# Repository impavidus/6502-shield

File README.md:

# 6502-shield

An Arduino shield that provides a 6502 cpu, ram, rom, and pio compactly.

## Project Status

I'm about to order the first prototype PCBs from OSH Park.  That means this PCB is completely untested and quite likely may burst into flames when powered on.  However, I am by no means here to tell you how to live your life so if you want to make one... =)

## Introduction

The 6502 shield provides (err will provide) most of the major components needed to implement a 6502 based computer.  Some of the key features.  This is aspirational and subject to change.

* Fully static design allows for single step execution of programs
* W65C02S - 8 bit CPU, W65C22 PIO controller, AT28BV256 256K EEPROM, AS6C62256 256K SRAM
* Full access to PIO PORTA and PORTB via header
* LCD header with potentiometer provides power, ground, and contrast adjust
* All components are leaded and reachable with mini-grabbers
* Support for optional DIP-8/4 3.3V External Crystal Oscillator
* Clock select jumper allows board to run from Internal FPGA clock or External XO
* LED status indicators for R/W, IRQ, CLK pins
* LED status indicators show when a devices address space is being accessed by the CPU (RAM/ROM/PIO/FPGA)
* FPGA manages chip enables based on user defined memory map.
* EEPROM write protection for EEPROM address space.
* EEPROM is programmed directly by Arduino asserting EEPROM_PGM line. This also disables EEPROM write protection in place during normal operation.
* DMA access from the Arduino to the 256K SRAM supported by asserting DMA line.
* FPGA clock supports run/halt/step via on-board push-button and slide switches.

## PCB

## Schematic

A PDF version of the schematic is <a href="docs/6502-shield-schematic.pdf">here</a>.

## System Block Diagram

## Source Files

All of the schematic capture and board layout work was done with Eagle.  The component libraries used, .sch, and .brd files are provided.

## CAM Files

All CAM files needed for PCB manufacturing including silkscreens, drills, etc. are provided.  In addition pick and place files and a Bill of Materials is provided in the CAMOutputs/Assembly folder.

## Models

The 3d model was done with AutoDesk Fusion.  The source file as well as .STEP file for the completed shield is provided.

## FPGA

The FPGA work is all going to be done in VHDL.  Once I begin writing it, I will add all of the source files, testbenches, etc. to the repository.

## 6502 Code

Also plan to provide some simple example assembly that demonstrates all the boards functions are working.  This will also be added to the repository.

## Acknowledgements

* Ben Eater - His breadboard computer projects are making homebrew cool again.  Ben's work heavily influenced my decision to attempt this project as well as inspiring me to make it all open and available for anyone.  If you're just getting started, please start with Ben's site, even if you don't build the breadboards yourself (but you should if at all possible) - seriously -  Thanks Ben.  < http://eater.net >

* Daryl Rictor - Thank you Daryl for sharing your Memory Decoder GAL based design to achieve a flexible memory map.  I am applying your approach in the FPGA of my design. < http://sbc.rictor.org/decoder.html >

* r/beneater - Pretty cool community even though I'm a lurker.  Seeing everybody else's builds made me give it a try, thanks for that everyone.  https://reddit.com/r/beneater

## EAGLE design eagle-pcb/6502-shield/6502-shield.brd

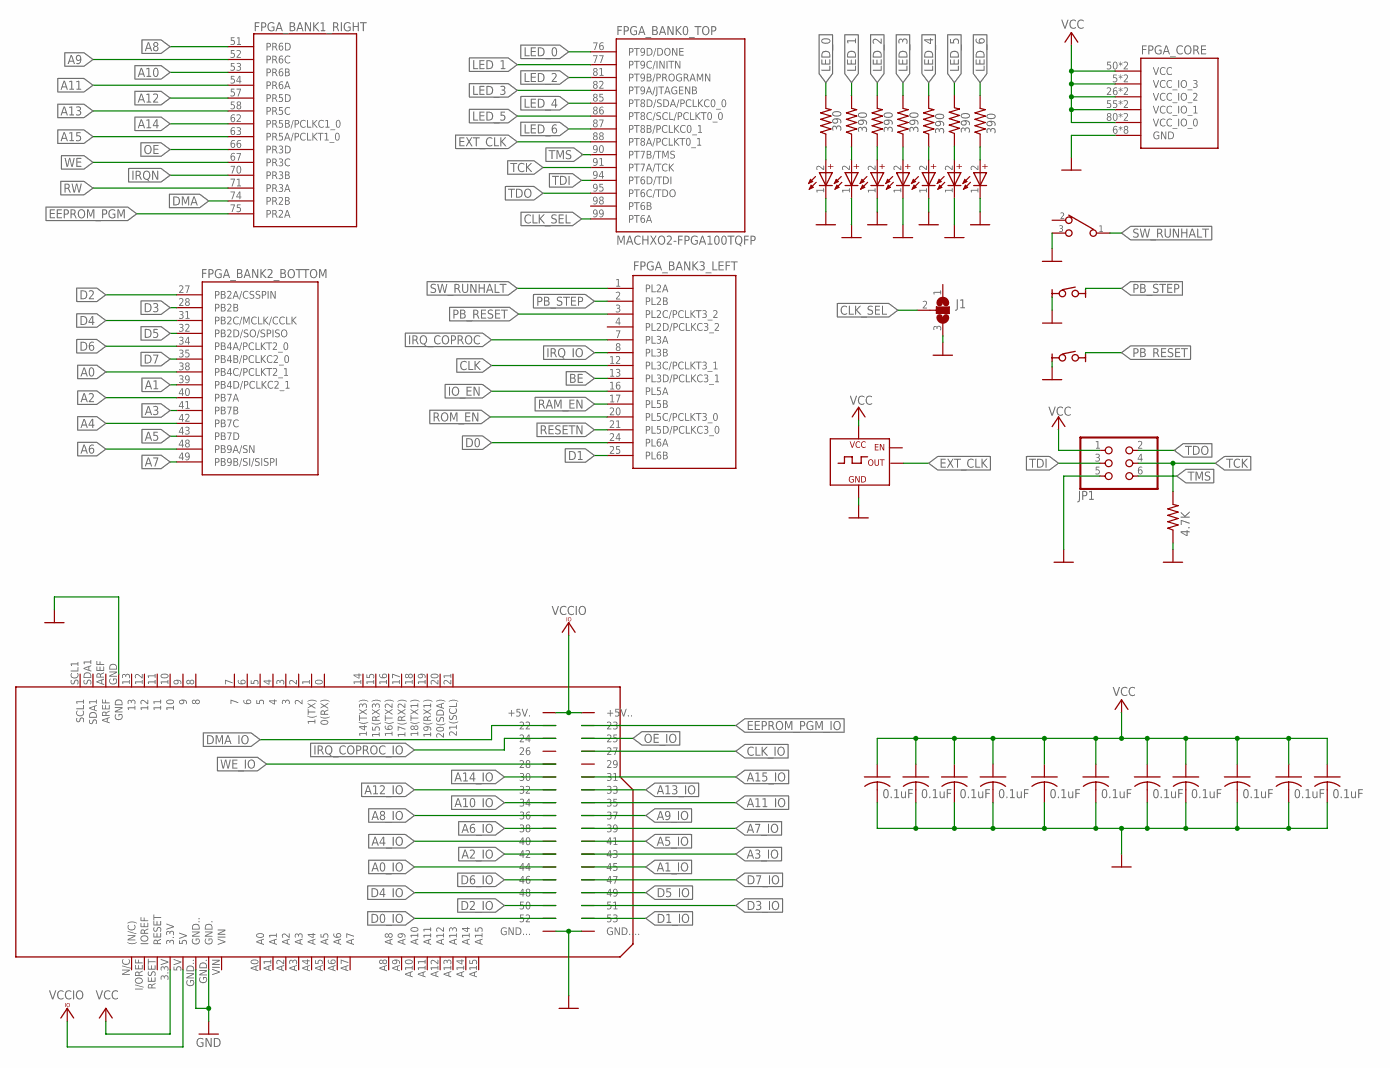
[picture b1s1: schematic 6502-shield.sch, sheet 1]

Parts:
C1, C2, C3, C4, C5, C6, C7, C20, C21, C22, C23: 0.1uF; C0805
D1, D2, D3, D4, D5, D6, D7: RED; WL-SMCD_0603
EXT_XO: CRYSTAL-OSC-DIP8/4; DIP8/4
FPGA: MACHXO2-FPGA100TQFP; QFP50P1600X1600X160-100N
J1: SJ2W; SJ_2
JP1: PINHD-2X3; 2X03
PB_RESET: MCSLPT4644B1TR-TACT-SW; MCSLPT4644B1TR-TACT-SW-NEW
PB_STEP: MCSLPT4644B1TR-TACT-SW; MCSLPT4644B1TR-TACT-SW-NEW
PCB1: ARDUINO_MEGA2560
R2, R4, R5, R6, R7, R8, R9: 390; R0603
R3: 4.7K; R0603
SW_RUNHALT: PCM12SMTR-SPDT-RIGHT-ANG; PCM12SMTR

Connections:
A0: FPGA.38 (PB4C/PCLKT2_1); also elsewhere on the board
A0_IO: PCB1.44; also elsewhere on the board
A1: FPGA.39 (PB4D/PCLKC2_1); also elsewhere on the board
A1_IO: PCB1.45; also elsewhere on the board
A2: FPGA.40 (PB7A); also elsewhere on the board
A2_IO: PCB1.42; also elsewhere on the board
A3: FPGA.41 (PB7B); also elsewhere on the board
A3_IO: PCB1.43; also elsewhere on the board
A4: FPGA.42 (PB7C); also elsewhere on the board
A4_IO: PCB1.40; also elsewhere on the board
A5: FPGA.43 (PB7D); also elsewhere on the board
A5_IO: PCB1.41; also elsewhere on the board
A6: FPGA.48 (PB9A/SN); also elsewhere on the board
A6_IO: PCB1.38; also elsewhere on the board
A7: FPGA.49 (PB9B/SI/SISPI); also elsewhere on the board
A7_IO: PCB1.39; also elsewhere on the board
A8: FPGA.51 (PR6D); also elsewhere on the board
A8_IO: PCB1.36; also elsewhere on the board
A9: FPGA.52 (PR6C); also elsewhere on the board
A9_IO: PCB1.37; also elsewhere on the board
A10: FPGA.53 (PR6B); also elsewhere on the board
A10_IO: PCB1.34; also elsewhere on the board
A11: FPGA.54 (PR6A); also elsewhere on the board
A11_IO: PCB1.35; also elsewhere on the board
A12: FPGA.57 (PR5D); also elsewhere on the board
A12_IO: PCB1.32; also elsewhere on the board
A13: FPGA.58 (PR5C); also elsewhere on the board
A13_IO: PCB1.33; also elsewhere on the board
A14: FPGA.62 (PR5B/PCLKC1_0); also elsewhere on the board
A14_IO: PCB1.30; also elsewhere on the board
A15: FPGA.63 (PR5A/PCLKT1_0); also elsewhere on the board
A15_IO: PCB1.31; also elsewhere on the board
BE: FPGA.13 (PL3D/PCLKC3_1); also elsewhere on the board
CLK: FPGA.12 (PL3C/PCLKT3_1); also elsewhere on the board
CLK_IO: PCB1.27; also elsewhere on the board
CLK_SEL: FPGA.99 (PT6A), J1.2
D0: FPGA.24 (PL6A); also elsewhere on the board
D0_IO: PCB1.52; also elsewhere on the board
D1: FPGA.25 (PL6B); also elsewhere on the board
D1_IO: PCB1.53; also elsewhere on the board
D2: FPGA.27 (PB2A/CSSPIN); also elsewhere on the board
D2_IO: PCB1.50; also elsewhere on the board
D3: FPGA.28 (PB2B); also elsewhere on the board
D3_IO: PCB1.51; also elsewhere on the board
D4: FPGA.31 (PB2C/MCLK/CCLK); also elsewhere on the board
D4_IO: PCB1.48; also elsewhere on the board
D5: FPGA.32 (PB2D/SO/SPISO); also elsewhere on the board
D5_IO: PCB1.49; also elsewhere on the board
D6: FPGA.34 (PB4A/PCLKT2_0); also elsewhere on the board
D6_IO: PCB1.46; also elsewhere on the board
D7: FPGA.35 (PB4B/PCLKC2_0); also elsewhere on the board
D7_IO: PCB1.47; also elsewhere on the board
DMA: FPGA.74 (PR2B); also elsewhere on the board
DMA_IO: PCB1.22; also elsewhere on the board
EEPROM_PGM: FPGA.75 (PR2A); also elsewhere on the board
EEPROM_PGM_IO: PCB1.23; also elsewhere on the board
EXT_CLK: EXT_XO.5 (OUT), FPGA.88 (PT8A/PCLKT0_1)
GND: C1.2, C2.2, C3.2, C4.2, C5.2, C6.2, C7.2, C20.2, C21.2, C22.2, C23.2, D1.1 (C), D2.1 (C), D3.1 (C), D4.1 (C), D5.1 (C), D6.1 (C), D7.1 (C), EXT_XO.4 (GND), FPGA.6 (GND), FPGA.22 (GND), FPGA.33 (GND), FPGA.44 (GND), FPGA.56 (GND), FPGA.72 (GND), FPGA.79 (GND), FPGA.92 (GND), J1.3, JP1.5, PB_RESET.T2, PB_STEP.T2, PCB1.GND, PCB1.GND., PCB1.GND.., PCB1.GND..., PCB1.GND...., R3.1, SW_RUNHALT.3; also elsewhere on the board
IO_EN: FPGA.16 (PL5A); also elsewhere on the board
IRQN: FPGA.70 (PR3B); also elsewhere on the board
IRQ_COPROC: FPGA.7 (PL3A); also elsewhere on the board
IRQ_COPROC_IO: PCB1.24; also elsewhere on the board
IRQ_IO: FPGA.8 (PL3B); also elsewhere on the board
LED_0: FPGA.76 (PT9D/DONE), R5.2
LED_1: FPGA.77 (PT9C/INITN), R6.2
LED_2: FPGA.81 (PT9B/PROGRAMN), R7.2
LED_3: FPGA.82 (PT9A/JTAGENB), R8.2
LED_4: FPGA.85 (PT8D/SDA/PCLKC0_0), R9.2
LED_5: FPGA.86 (PT8C/SCL/PCLKT0_0), R4.2
LED_6: FPGA.87 (PT8B/PCLKC0_1), R2.2
unnamed: D1.2 (A), R5.1
unnamed: D2.2 (A), R6.1
unnamed: D5.2 (A), R7.1
unnamed: D4.2 (A), R8.1
unnamed: D3.2 (A), R9.1
unnamed: D6.2 (A), R4.1
unnamed: D7.2 (A), R2.1
OE: FPGA.66 (PR3D); also elsewhere on the board
OE_IO: PCB1.25; also elsewhere on the board
PB_RESET: FPGA.3 (PL2C/PCLKT3_2), PB_RESET.T3
PB_STEP: FPGA.2 (PL2B), PB_STEP.T3
RAM_EN: FPGA.17 (PL5B); also elsewhere on the board
RESETN: FPGA.21 (PL5D/PCLKC3_0); also elsewhere on the board
ROM_EN: FPGA.20 (PL5C/PCLKT3_0); also elsewhere on the board
RW: FPGA.71 (PR3A); also elsewhere on the board
SW_RUNHALT: FPGA.1 (PL2A), SW_RUNHALT.1
TCK: FPGA.91 (PT7A/TCK), JP1.4, R3.2
TDI: FPGA.94 (PT6D/TDI), JP1.3
TDO: FPGA.95 (PT6C/TDO), JP1.2
TMS: FPGA.90 (PT7B/TMS), JP1.6
VCC: C1.1, C2.1, C3.1, C4.1, C5.1, C6.1, C7.1, C20.1, C21.1, C22.1, C23.1, EXT_XO.8 (VCC), FPGA.5 (VCC_IO_3), FPGA.23 (VCC_IO_3), FPGA.26 (VCC_IO_2), FPGA.46 (VCC_IO_2), FPGA.50 (VCC), FPGA.55 (VCC_IO_1), FPGA.73 (VCC_IO_1), FPGA.80 (VCC_IO_0), FPGA.93 (VCC_IO_0), FPGA.100 (VCC), JP1.1, PCB1.3.3V; also elsewhere on the board
VCCIO: PCB1.5V, PCB1.5V. (+5V.), PCB1.5V.. (+5V..); also elsewhere on the board
WE: FPGA.67 (PR3C); also elsewhere on the board
WE_IO: PCB1.28; also elsewhere on the board

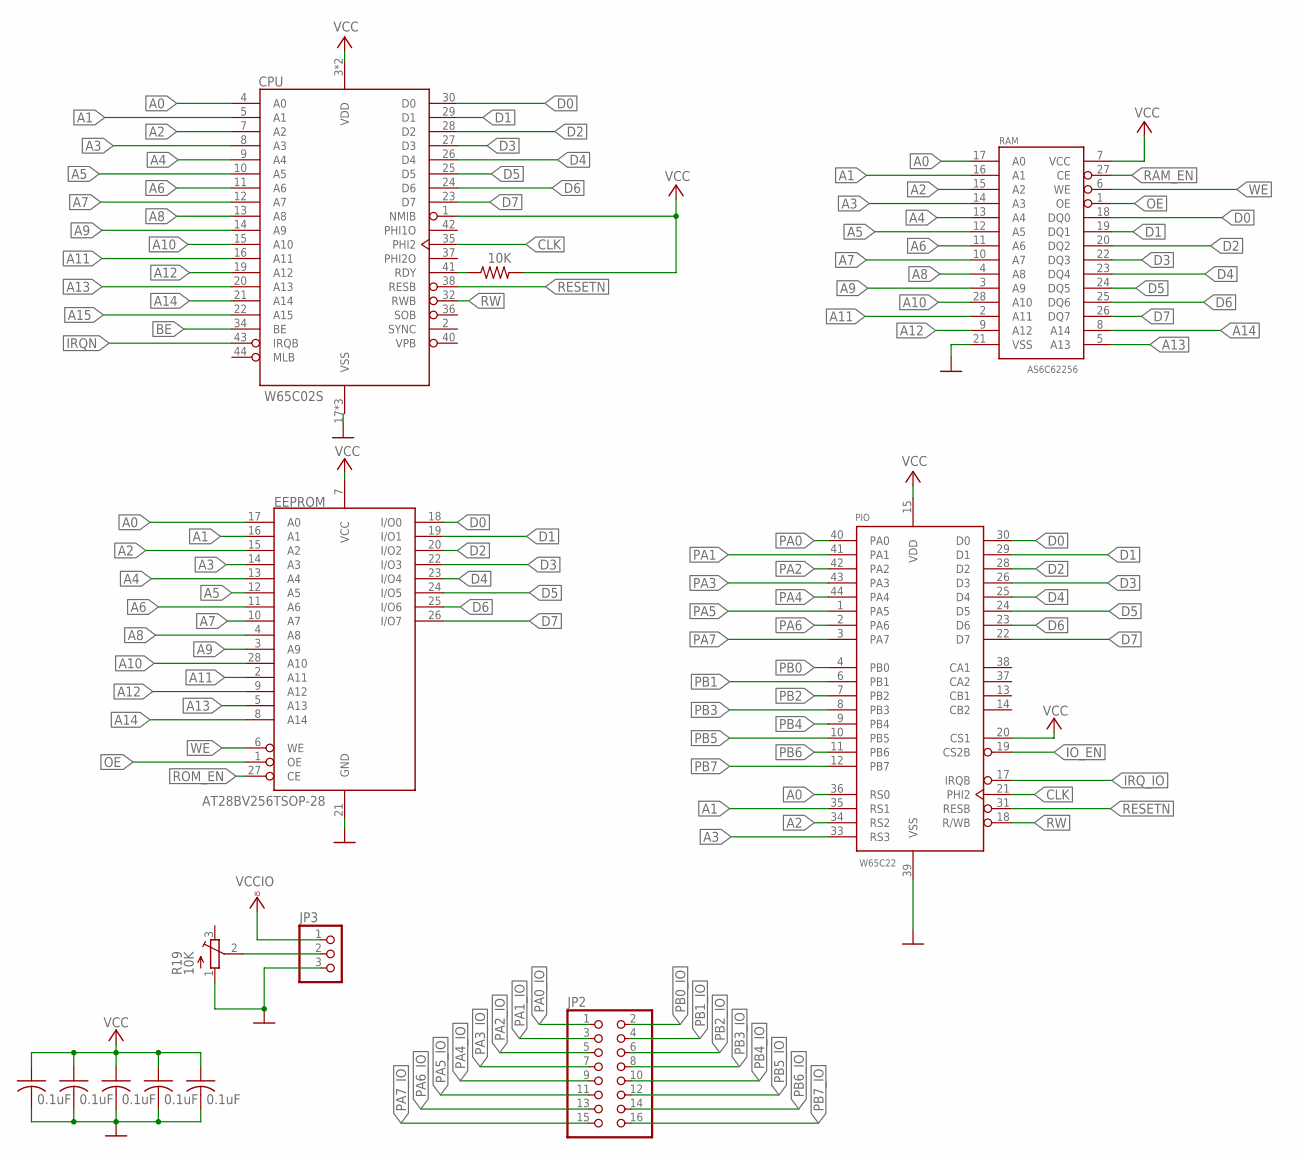
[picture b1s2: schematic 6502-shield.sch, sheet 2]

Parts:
C24, C25, C26, C27, C28: 0.1uF; C0805
CPU: W65C02S; QFP80P1320X1320X270-44N
EEPROM: AT28BV256TSOP-28; SOP55P1340X120-28N
JP2: PINHD-2X8; 2X08
JP3: PINHD-1X3; 1X03
PIO: W65C22; QFP80P1320X1320X270-44N
R18: 10K; R0603
R19: 10K; TC33X
RAM: AS6C62256; SOP55P1340X120-28N

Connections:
A0: CPU.4 (A0), EEPROM.17 (A0), PIO.36 (RS0), RAM.17 (A0); also elsewhere on the board
A1: CPU.5 (A1), EEPROM.16 (A1), PIO.35 (RS1), RAM.16 (A1); also elsewhere on the board
A2: CPU.7 (A2), EEPROM.15 (A2), PIO.34 (RS2), RAM.15 (A2); also elsewhere on the board
A3: CPU.8 (A3), EEPROM.14 (A3), PIO.33 (RS3), RAM.14 (A3); also elsewhere on the board
A4: CPU.9 (A4), EEPROM.13 (A4), RAM.13 (A4); also elsewhere on the board
A5: CPU.10 (A5), EEPROM.12 (A5), RAM.12 (A5); also elsewhere on the board
A6: CPU.11 (A6), EEPROM.11 (A6), RAM.11 (A6); also elsewhere on the board
A7: CPU.12 (A7), EEPROM.10 (A7), RAM.10 (A7); also elsewhere on the board
A8: CPU.13 (A8), EEPROM.4 (A8), RAM.4 (A8); also elsewhere on the board
A9: CPU.14 (A9), EEPROM.3 (A9), RAM.3 (A9); also elsewhere on the board
A10: CPU.15 (A10), EEPROM.28 (A10), RAM.28 (A10); also elsewhere on the board
A11: CPU.16 (A11), EEPROM.2 (A11), RAM.2 (A11); also elsewhere on the board
A12: CPU.19 (A12), EEPROM.9 (A12), RAM.9 (A12); also elsewhere on the board
A13: CPU.20 (A13), EEPROM.5 (A13), RAM.5 (A13); also elsewhere on the board
A14: CPU.21 (A14), EEPROM.8 (A14), RAM.8 (A14); also elsewhere on the board
A15: CPU.22 (A15); also elsewhere on the board
BE: CPU.34 (BE); also elsewhere on the board
CLK: CPU.35 (PHI2), PIO.21 (PHI2); also elsewhere on the board
D0: CPU.30 (D0), EEPROM.18 (I/O0), PIO.30 (D0), RAM.18 (DQ0); also elsewhere on the board
D1: CPU.29 (D1), EEPROM.19 (I/O1), PIO.29 (D1), RAM.19 (DQ1); also elsewhere on the board
D2: CPU.28 (D2), EEPROM.20 (I/O2), PIO.28 (D2), RAM.20 (DQ2); also elsewhere on the board
D3: CPU.27 (D3), EEPROM.22 (I/O3), PIO.26 (D3), RAM.22 (DQ3); also elsewhere on the board
D4: CPU.26 (D4), EEPROM.23 (I/O4), PIO.25 (D4), RAM.23 (DQ4); also elsewhere on the board
D5: CPU.25 (D5), EEPROM.24 (I/O5), PIO.24 (D5), RAM.24 (DQ5); also elsewhere on the board
D6: CPU.24 (D6), EEPROM.25 (I/O6), PIO.23 (D6), RAM.25 (DQ6); also elsewhere on the board
D7: CPU.23 (D7), EEPROM.26 (I/O7), PIO.22 (D7), RAM.26 (DQ7); also elsewhere on the board
GND: C24.2, C25.2, C26.2, C27.2, C28.2, EEPROM.21 (GND), JP3.3, PIO.39 (VSS), R19.1 (A), RAM.21 (VSS); also elsewhere on the board
IO_EN: PIO.19 (CS2B); also elsewhere on the board
IRQN: CPU.43 (IRQB); also elsewhere on the board
IRQ_IO: PIO.17 (IRQB); also elsewhere on the board
unnamed: CPU.41 (RDY), R18.1
unnamed: JP3.2, R19.2 (S)
OE: EEPROM.1 (OE), RAM.1 (OE); also elsewhere on the board
PA0: PIO.40 (PA0); also elsewhere on the board
PA0_IO: JP2.1; also elsewhere on the board
PA1: PIO.41 (PA1); also elsewhere on the board
PA1_IO: JP2.3; also elsewhere on the board
PA2: PIO.42 (PA2); also elsewhere on the board
PA2_IO: JP2.5; also elsewhere on the board
PA3: PIO.43 (PA3); also elsewhere on the board
PA3_IO: JP2.7; also elsewhere on the board
PA4: PIO.44 (PA4); also elsewhere on the board
PA4_IO: JP2.9; also elsewhere on the board
PA5: PIO.1 (PA5); also elsewhere on the board
PA5_IO: JP2.11; also elsewhere on the board
PA6: PIO.2 (PA6); also elsewhere on the board
PA6_IO: JP2.13; also elsewhere on the board
PA7: PIO.3 (PA7); also elsewhere on the board
PA7_IO: JP2.15; also elsewhere on the board
PB0: PIO.4 (PB0); also elsewhere on the board
PB0_IO: JP2.2; also elsewhere on the board
PB1: PIO.6 (PB1); also elsewhere on the board
PB1_IO: JP2.4; also elsewhere on the board
PB2: PIO.7 (PB2); also elsewhere on the board
PB2_IO: JP2.6; also elsewhere on the board
PB3: PIO.8 (PB3); also elsewhere on the board
PB3_IO: JP2.8; also elsewhere on the board
PB4: PIO.9 (PB4); also elsewhere on the board
PB4_IO: JP2.10; also elsewhere on the board
PB5: PIO.10 (PB5); also elsewhere on the board
PB5_IO: JP2.12; also elsewhere on the board
PB6: PIO.11 (PB6); also elsewhere on the board
PB6_IO: JP2.14; also elsewhere on the board
PB7: PIO.12 (PB7); also elsewhere on the board
PB7_IO: JP2.16; also elsewhere on the board
RAM_EN: RAM.27 (CE); also elsewhere on the board
RESETN: CPU.38 (RESB), PIO.31 (RESB); also elsewhere on the board
ROM_EN: EEPROM.27 (CE); also elsewhere on the board
RW: CPU.32 (RWB), PIO.18 (R/WB); also elsewhere on the board
VCC: C24.1, C25.1, C26.1, C27.1, C28.1, CPU.1 (NMIB), CPU.3 (VDD), CPU.31 (VDD), EEPROM.7 (VCC), PIO.15 (VDD), PIO.20 (CS1), R18.2, RAM.7 (VCC); also elsewhere on the board
VCCIO: JP3.1; also elsewhere on the board
WE: EEPROM.6 (WE), RAM.6 (WE); also elsewhere on the board

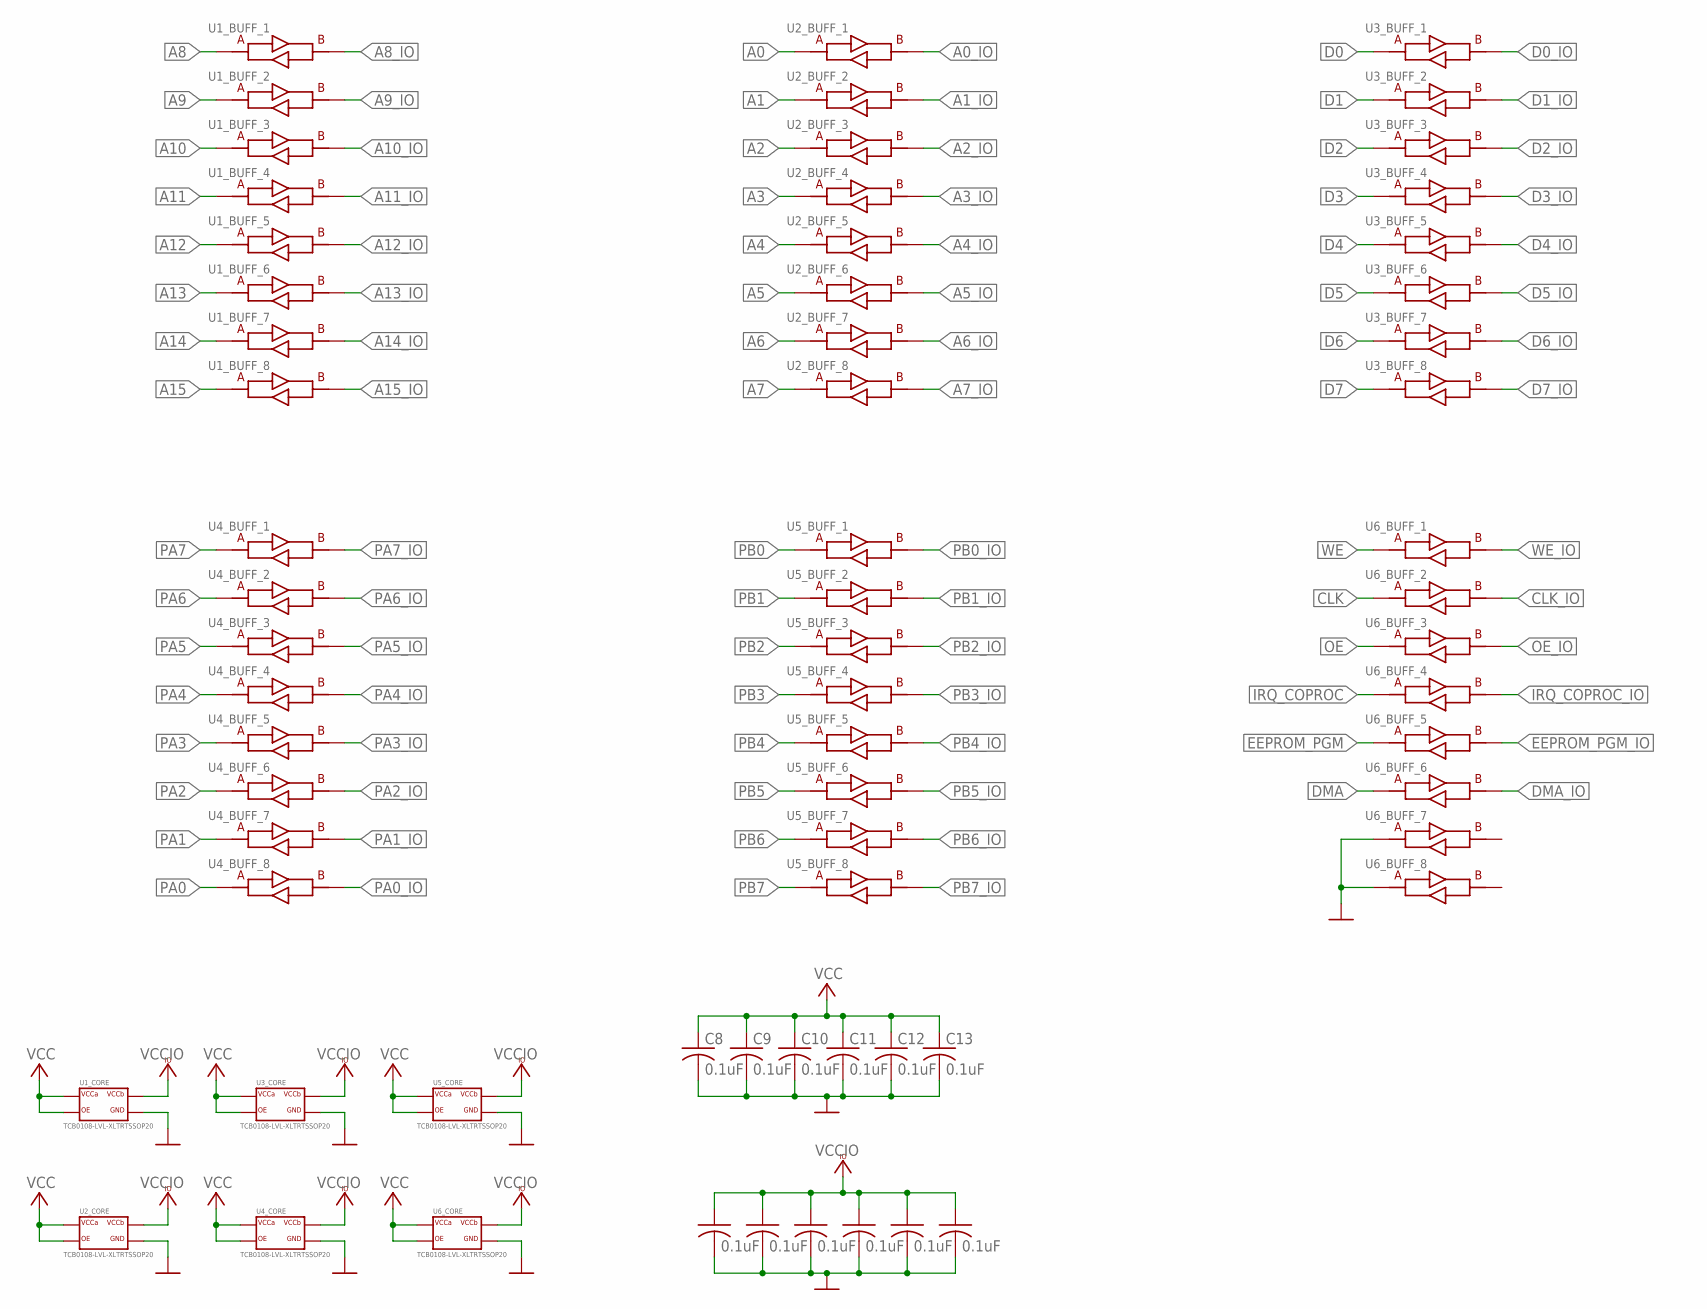
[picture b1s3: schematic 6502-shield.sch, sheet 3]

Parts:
C8, C9, C10, C11, C12, C13, C14, C15, C16, C17, C18, C19: 0.1uF; C0805
U1, U2, U3, U4, U5, U6: TCB0108-LVL-XLTRTSSOP20; SOP65P640X120-20N

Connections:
A0: U2.1 (A); also elsewhere on the board
A0_IO: U2.20 (B); also elsewhere on the board
A1: U2.3 (A); also elsewhere on the board
A1_IO: U2.18 (B); also elsewhere on the board
A2: U2.4 (A); also elsewhere on the board
A2_IO: U2.17 (B); also elsewhere on the board
A3: U2.5 (A); also elsewhere on the board
A3_IO: U2.16 (B); also elsewhere on the board
A4: U2.6 (A); also elsewhere on the board
A4_IO: U2.15 (B); also elsewhere on the board
A5: U2.7 (A); also elsewhere on the board
A5_IO: U2.14 (B); also elsewhere on the board
A6: U2.8 (A); also elsewhere on the board
A6_IO: U2.13 (B); also elsewhere on the board
A7: U2.9 (A); also elsewhere on the board
A7_IO: U2.12 (B); also elsewhere on the board
A8: U1.1 (A); also elsewhere on the board
A8_IO: U1.20 (B); also elsewhere on the board
A9: U1.3 (A); also elsewhere on the board
A9_IO: U1.18 (B); also elsewhere on the board
A10: U1.4 (A); also elsewhere on the board
A10_IO: U1.17 (B); also elsewhere on the board
A11: U1.5 (A); also elsewhere on the board
A11_IO: U1.16 (B); also elsewhere on the board
A12: U1.6 (A); also elsewhere on the board
A12_IO: U1.15 (B); also elsewhere on the board
A13: U1.7 (A); also elsewhere on the board
A13_IO: U1.14 (B); also elsewhere on the board
A14: U1.8 (A); also elsewhere on the board
A14_IO: U1.13 (B); also elsewhere on the board
A15: U1.9 (A); also elsewhere on the board
A15_IO: U1.12 (B); also elsewhere on the board
CLK: U6.3 (A); also elsewhere on the board
CLK_IO: U6.18 (B); also elsewhere on the board
D0: U3.1 (A); also elsewhere on the board
D0_IO: U3.20 (B); also elsewhere on the board
D1: U3.3 (A); also elsewhere on the board
D1_IO: U3.18 (B); also elsewhere on the board
D2: U3.4 (A); also elsewhere on the board
D2_IO: U3.17 (B); also elsewhere on the board
D3: U3.5 (A); also elsewhere on the board
D3_IO: U3.16 (B); also elsewhere on the board
D4: U3.6 (A); also elsewhere on the board
D4_IO: U3.15 (B); also elsewhere on the board
D5: U3.7 (A); also elsewhere on the board
D5_IO: U3.14 (B); also elsewhere on the board
D6: U3.8 (A); also elsewhere on the board
D6_IO: U3.13 (B); also elsewhere on the board
D7: U3.9 (A); also elsewhere on the board
D7_IO: U3.12 (B); also elsewhere on the board
DMA: U6.7 (A); also elsewhere on the board
DMA_IO: U6.14 (B); also elsewhere on the board
EEPROM_PGM: U6.6 (A); also elsewhere on the board
EEPROM_PGM_IO: U6.15 (B); also elsewhere on the board
GND: C8.2, C9.2, C10.2, C11.2, C12.2, C13.2, C14.2, C15.2, C16.2, C17.2, C18.2, C19.2, U1.11 (GND), U2.11 (GND), U3.11 (GND), U4.11 (GND), U5.11 (GND), U6.8 (A), U6.9 (A), U6.11 (GND); also elsewhere on the board
IRQ_COPROC: U6.5 (A); also elsewhere on the board
IRQ_COPROC_IO: U6.16 (B); also elsewhere on the board
OE: U6.4 (A); also elsewhere on the board
OE_IO: U6.17 (B); also elsewhere on the board
PA0: U4.9 (A); also elsewhere on the board
PA0_IO: U4.12 (B); also elsewhere on the board
PA1: U4.8 (A); also elsewhere on the board
PA1_IO: U4.13 (B); also elsewhere on the board
PA2: U4.7 (A); also elsewhere on the board
PA2_IO: U4.14 (B); also elsewhere on the board
PA3: U4.6 (A); also elsewhere on the board
PA3_IO: U4.15 (B); also elsewhere on the board
PA4: U4.5 (A); also elsewhere on the board
PA4_IO: U4.16 (B); also elsewhere on the board
PA5: U4.4 (A); also elsewhere on the board
PA5_IO: U4.17 (B); also elsewhere on the board
PA6: U4.3 (A); also elsewhere on the board
PA6_IO: U4.18 (B); also elsewhere on the board
PA7: U4.1 (A); also elsewhere on the board
PA7_IO: U4.20 (B); also elsewhere on the board
PB0: U5.1 (A); also elsewhere on the board
PB0_IO: U5.20 (B); also elsewhere on the board
PB1: U5.3 (A); also elsewhere on the board
PB1_IO: U5.18 (B); also elsewhere on the board
PB2: U5.4 (A); also elsewhere on the board
PB2_IO: U5.17 (B); also elsewhere on the board
PB3: U5.5 (A); also elsewhere on the board
PB3_IO: U5.16 (B); also elsewhere on the board
PB4: U5.6 (A); also elsewhere on the board
PB4_IO: U5.15 (B); also elsewhere on the board
PB5: U5.7 (A); also elsewhere on the board
PB5_IO: U5.14 (B); also elsewhere on the board
PB6: U5.8 (A); also elsewhere on the board
PB6_IO: U5.13 (B); also elsewhere on the board
PB7: U5.9 (A); also elsewhere on the board
PB7_IO: U5.12 (B); also elsewhere on the board
VCC: C8.1, C9.1, C10.1, C11.1, C12.1, C13.1, U1.2 (VCC_A), U1.10 (OE), U2.2 (VCC_A), U2.10 (OE), U3.2 (VCC_A), U3.10 (OE), U4.2 (VCC_A), U4.10 (OE), U5.2 (VCC_A), U5.10 (OE), U6.2 (VCC_A), U6.10 (OE); also elsewhere on the board
VCCIO: C14.1, C15.1, C16.1, C17.1, C18.1, C19.1, U1.19 (VCC_B), U2.19 (VCC_B), U3.19 (VCC_B), U4.19 (VCC_B), U5.19 (VCC_B), U6.19 (VCC_B); also elsewhere on the board
WE: U6.1 (A); also elsewhere on the board
WE_IO: U6.20 (B); also elsewhere on the board

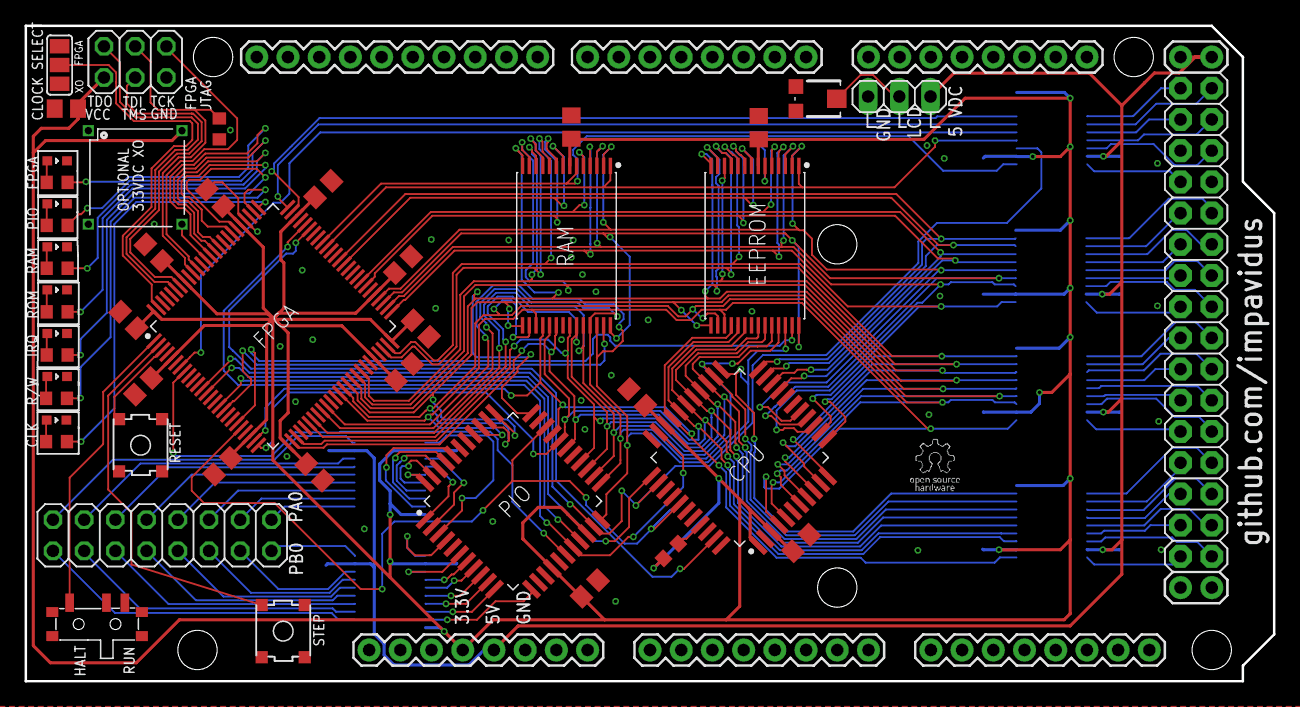
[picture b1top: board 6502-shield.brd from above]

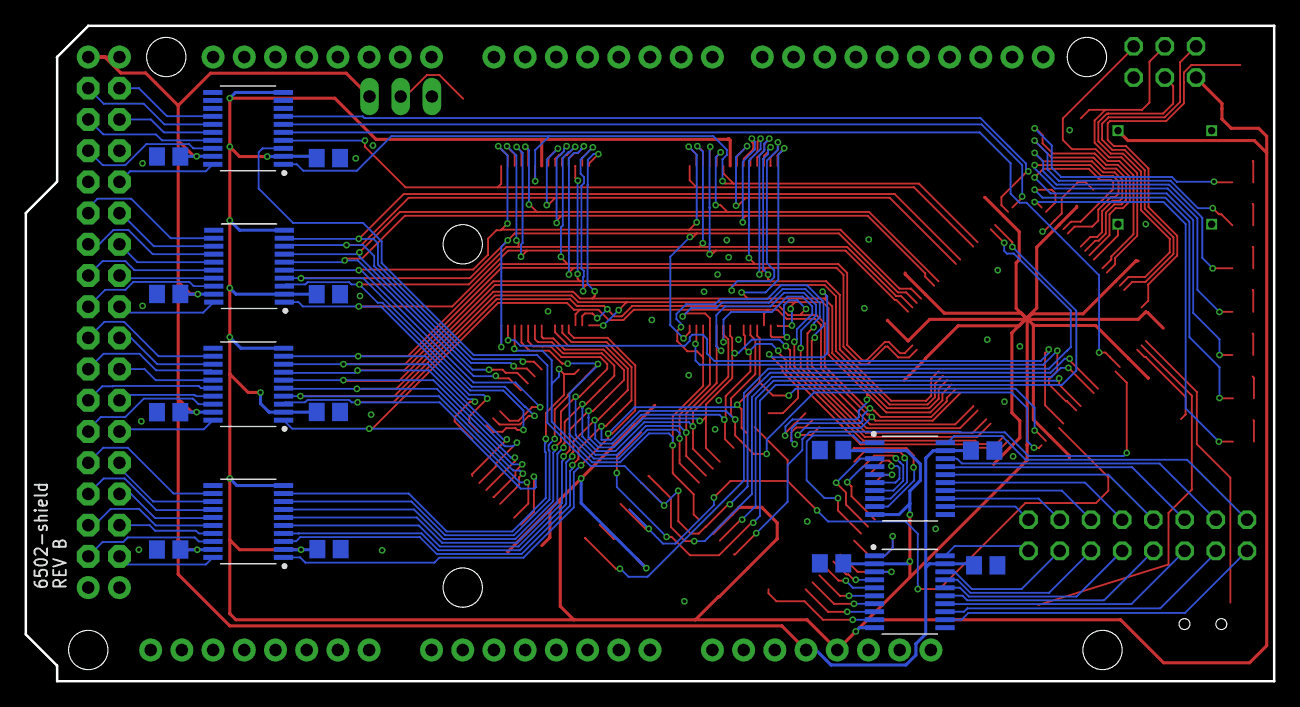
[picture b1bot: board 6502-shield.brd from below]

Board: 2 copper layers, 101.6 x 53.3 mm, 66 parts (18 on the bottom side), 128 nets.

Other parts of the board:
U$1: OSHW_LOGO; OSHW_LOGO@1

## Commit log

2020-03-23 Basic project setup and a library. Added some stuff to the library.
2020-04-02 Dead end =(
2020-04-02 forgot some stuff
2020-04-02 pulling the plug on discrete timers and gates to replace with FPGA =( Can't make it fit on a shield with a 2 layer pwb.
2020-04-02 Put pretty in readme
2020-04-02 added lattice machx02-256 FPGA in tqfp100 package - symbol, footprint, 3d model
2020-04-02 adding drc files with rules suitable for reasonable manufacturing, same with rules for gerbers in cam file
2020-04-05 got the fpga based design done (first pass). Notional parts placement, no routing.
2020-04-05 apparently I'm not gitting it... git it? git it? oh boy...
2020-04-05 yolo
2020-04-10 fully routed, getting close
2020-04-10 This should be ready to send out.
2020-04-10 updated gitignore to not ignore cam files
2020-04-10 Added some more docs
2020-04-17 getting the basic project structure setup and hdl entity definition.
2020-04-19 Started a test bench, got the test harness in place along with a test for the clk_select feature. Added clk_select feature to the implementation.
2020-04-23 Fixed problems with FPGA pinout in component library, updated schematic and cleaned it up a bunch. Fixed external clock not coming into FPGA on dedicated clock net pin. More schematic work on the lis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
2020-04-25 Bunch of work on rev b. but more to do.
2020-04-26 More routing work on the pcb, lots more left... yay =/
2020-04-26 The fpga is now fully broken out and mostly routed, edges of board are routed so pretty much just the busses left to do.
2020-04-26 more routing work on the pcb but not quite there yet.
2020-04-28 Board is routed w/ no erc or drc errors.
2020-04-30 Made some tweaks and random clean up. Updating the images and a system block diagram.
2020-04-30 Generated new gerbers, bom, pick & place. Generated new 3d models.
2020-05-03 fixed. verified footprint with the printer. still need to generate new camoutputs, etc.
2020-05-04 Overlooked that tactile switch pads were very small for hand soldering so enlarged them. Created new models, gerbers, and images.
2020-05-05 Added some more silkscreen
2020-05-19 This commit (and branch) got a little bigger than planned. Added bus activity monitor component to debounce switches and drive leds with pwm - both through a register interface to the rest of the des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
2020-05-20 Some code clean up and formatting.

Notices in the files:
parts and their libraries:
we-led: Copyright: Würth Elektronik
